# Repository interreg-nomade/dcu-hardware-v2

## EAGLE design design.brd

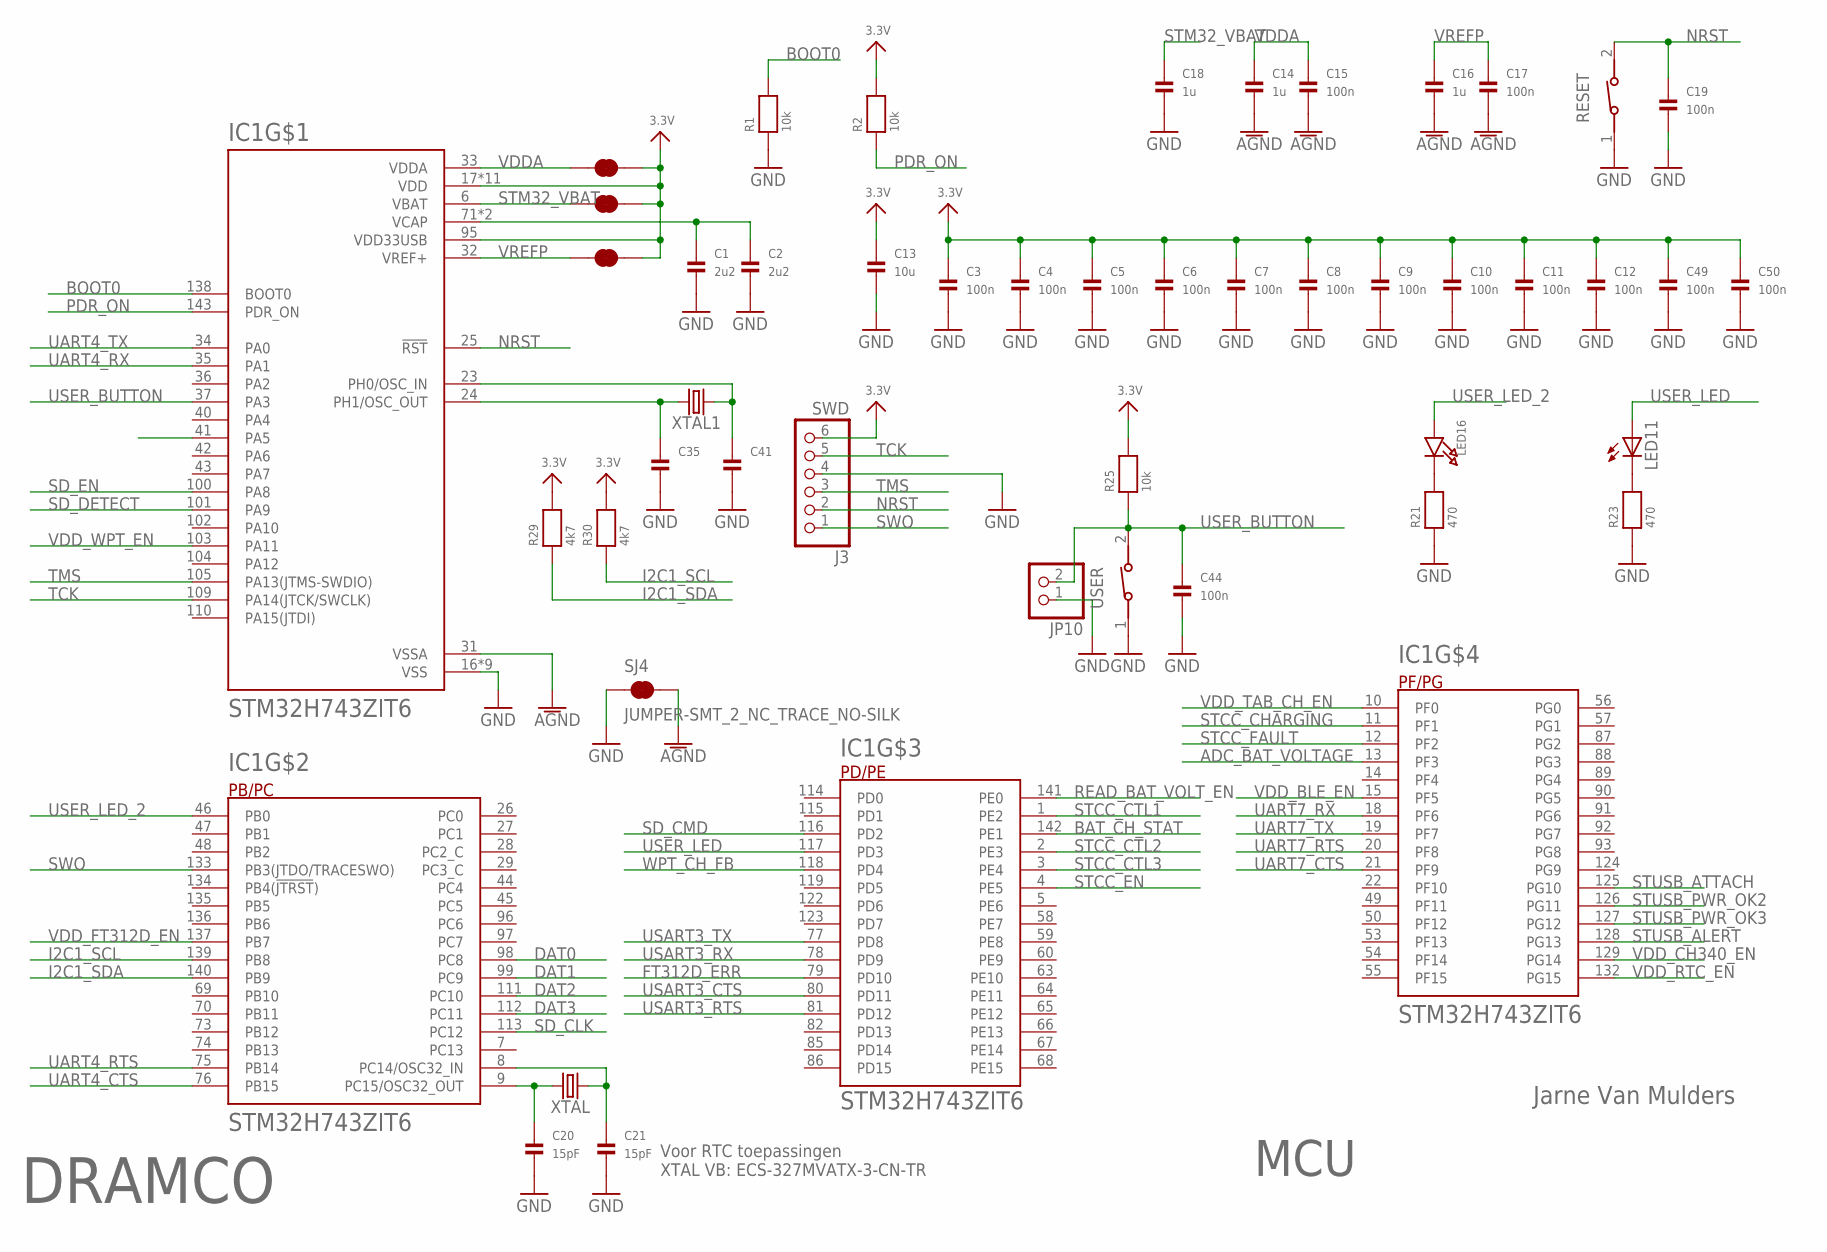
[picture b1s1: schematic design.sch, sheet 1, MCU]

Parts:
C1, C2: 2u2; 0805
C3, C4, C5, C6, C7, C8, C9, C10, C11, C12, C15, C17, C19, C44, C49, C50: 100n; 0603
C13: 10u; 0805
C14, C16, C18: 1u; 0603
C20, C21: 15pF; 0603
C35, C41: CAP_CERAMIC0603; 0603
IC1: STM32H743ZIT6; QFP50P2200X2200X160-144N
J3: SWD; 1X06_ROUND
JP10: HEADER-1X2ROUND; 1X02_ROUND
LED11: LED3MM
LED16: LED0805; CHIPLED_0805
R1, R2, R25: 10k; 0603
R21, R23: 470; 0603
R29, R30: 4k7; 0603
RESET: 434111043826
SJ1, SJ2, SJ3, SJ4: JUMPER-SMT_2_NC_TRACE_NO-SILK; SMT-JUMPER_2_NC_TRACE_NO-SILK
USER: 434111043826
XTAL, XTAL1: CRYSTALSMD-3.2X2.5; CRYSTAL-SMD-3.2X2.5MM

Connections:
3.3V: C3.1, C4.1, C5.1, C6.1, C7.1, C8.1, C9.1, C10.1, C11.1, C12.1, C13.1, C49.1, C50.1, IC1.17 (VDD), IC1.30 (VDD), IC1.39 (VDD), IC1.52 (VDD), IC1.62 (VDD), IC1.72 (VDD), IC1.84 (VDD), IC1.95 (VDD33USB), IC1.108 (VDD), IC1.121 (VDD), IC1.131 (VDD), IC1.144 (VDD), J3.6, R2.2, R25.2, R29.2, R30.2, SJ1.2, SJ2.2, SJ3.2; also elsewhere on the board
ADC_BAT_VOLTAGE: IC1.13 (PF3); also elsewhere on the board
AGND: C14.2, C15.2, C16.2, C17.2, IC1.31 (VSSA), SJ4.2
BAT_CH_STAT: IC1.142 (PE1); also elsewhere on the board
BOOT0: IC1.138 (BOOT0), R1.2
DAT0: IC1.98 (PC8); also elsewhere on the board
DAT1: IC1.99 (PC9); also elsewhere on the board
DAT2: IC1.111 (PC10); also elsewhere on the board
DAT3: IC1.112 (PC11); also elsewhere on the board
FT312D_ERR: IC1.79 (PD10); also elsewhere on the board
GND: C1.2, C2.2, C3.2, C4.2, C5.2, C6.2, C7.2, C8.2, C9.2, C10.2, C11.2, C12.2, C13.2, C18.2, C19.2, C20.2, C21.2, C35.2, C41.2, C44.2, C49.2, C50.2, IC1.16 (VSS), IC1.38 (VSS), IC1.51 (VSS), IC1.61 (VSS), IC1.83 (VSS), IC1.94 (VSS), IC1.107 (VSS), IC1.120 (VSS), IC1.130 (VSS), J3.4, JP10.1, R1.1, R21.1, R23.1, RESET.1, SJ4.1, USER.1; also elsewhere on the board
I2C1_SCL: IC1.139 (PB8), R30.1; also elsewhere on the board
I2C1_SDA: IC1.140 (PB9), R29.1; also elsewhere on the board
unnamed: C1.1, C2.1, IC1.71 (VCAP), IC1.106 (VCAP)
unnamed: C20.1, IC1.9 (PC15/OSC32_OUT), XTAL.3 (2)
unnamed: C21.1, IC1.8 (PC14/OSC32_IN), XTAL.1
unnamed: LED16.C, R21.2
unnamed: C35.1, IC1.24 (PH1/OSC_OUT), XTAL1.3 (2)
unnamed: LED11.K (C), R23.2
unnamed: C41.1, IC1.23 (PH0/OSC_IN), XTAL1.1
NRST: C19.1, IC1.25 (!RST), J3.2, RESET.2
PDR_ON: IC1.143 (PDR_ON), R2.1
READ_BAT_VOLT_EN: IC1.141 (PE0); also elsewhere on the board
SD_CLK: IC1.113 (PC12); also elsewhere on the board
SD_CMD: IC1.116 (PD2); also elsewhere on the board
SD_DETECT: IC1.101 (PA9); also elsewhere on the board
SD_EN: IC1.100 (PA8); also elsewhere on the board
STCC_CHARGING: IC1.11 (PF1); also elsewhere on the board
STCC_CTL1: IC1.1 (PE2); also elsewhere on the board
STCC_CTL2: IC1.2 (PE3); also elsewhere on the board
STCC_CTL3: IC1.3 (PE4); also elsewhere on the board
STCC_EN: IC1.4 (PE5); also elsewhere on the board
STCC_FAULT: IC1.12 (PF2); also elsewhere on the board
STM32_VBAT: C18.1, IC1.6 (VBAT), SJ2.1
STUSB_ALERT: IC1.128 (PG13); also elsewhere on the board
STUSB_ATTACH: IC1.125 (PG10); also elsewhere on the board
STUSB_PWR_OK2: IC1.126 (PG11); also elsewhere on the board
STUSB_PWR_OK3: IC1.127 (PG12); also elsewhere on the board
SWO: IC1.133 (PB3(JTDO/TRACESWO)), J3.1
TCK: IC1.109 (PA14(JTCK/SWCLK)), J3.5
TMS: IC1.105 (PA13(JTMS-SWDIO)), J3.3
UART4_CTS: IC1.76 (PB15); also elsewhere on the board
UART4_RTS: IC1.75 (PB14); also elsewhere on the board
UART4_RX: IC1.35 (PA1); also elsewhere on the board
UART4_TX: IC1.34 (PA0); also elsewhere on the board
UART7_CTS: IC1.21 (PF9); also elsewhere on the board
UART7_RTS: IC1.20 (PF8); also elsewhere on the board
UART7_RX: IC1.18 (PF6); also elsewhere on the board
UART7_TX: IC1.19 (PF7); also elsewhere on the board
USART3_CTS: IC1.80 (PD11); also elsewhere on the board
USART3_RTS: IC1.81 (PD12); also elsewhere on the board
USART3_RX: IC1.78 (PD9); also elsewhere on the board
USART3_TX: IC1.77 (PD8); also elsewhere on the board
USER_BUTTON: C44.1, IC1.37 (PA3), JP10.2, R25.1, USER.2
USER_LED: IC1.117 (PD3), LED11.A
USER_LED_2: IC1.46 (PB0), LED16.A
VDDA: C14.1, C15.1, IC1.33 (VDDA), SJ3.1
VDD_BLE_EN: IC1.15 (PF5); also elsewhere on the board
VDD_CH340_EN: IC1.129 (PG14); also elsewhere on the board
VDD_FT312D_EN: IC1.137 (PB7); also elsewhere on the board
VDD_NRF_EN: IC1.41 (PA5)
VDD_RTC_EN: IC1.132 (PG15); also elsewhere on the board
VDD_TAB_CH_EN: IC1.10 (PF0); also elsewhere on the board
VDD_WPT_EN: IC1.103 (PA11); also elsewhere on the board
VREFP: C16.1, C17.1, IC1.32 (VREF+), SJ1.1
WPT_CH_FB: IC1.118 (PD4); also elsewhere on the board

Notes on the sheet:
Voor RTC toepassingen XTAL VB: ECS-327MVATX-3-CN-TR
MCU
Jarne Van Mulders
DRAMCO

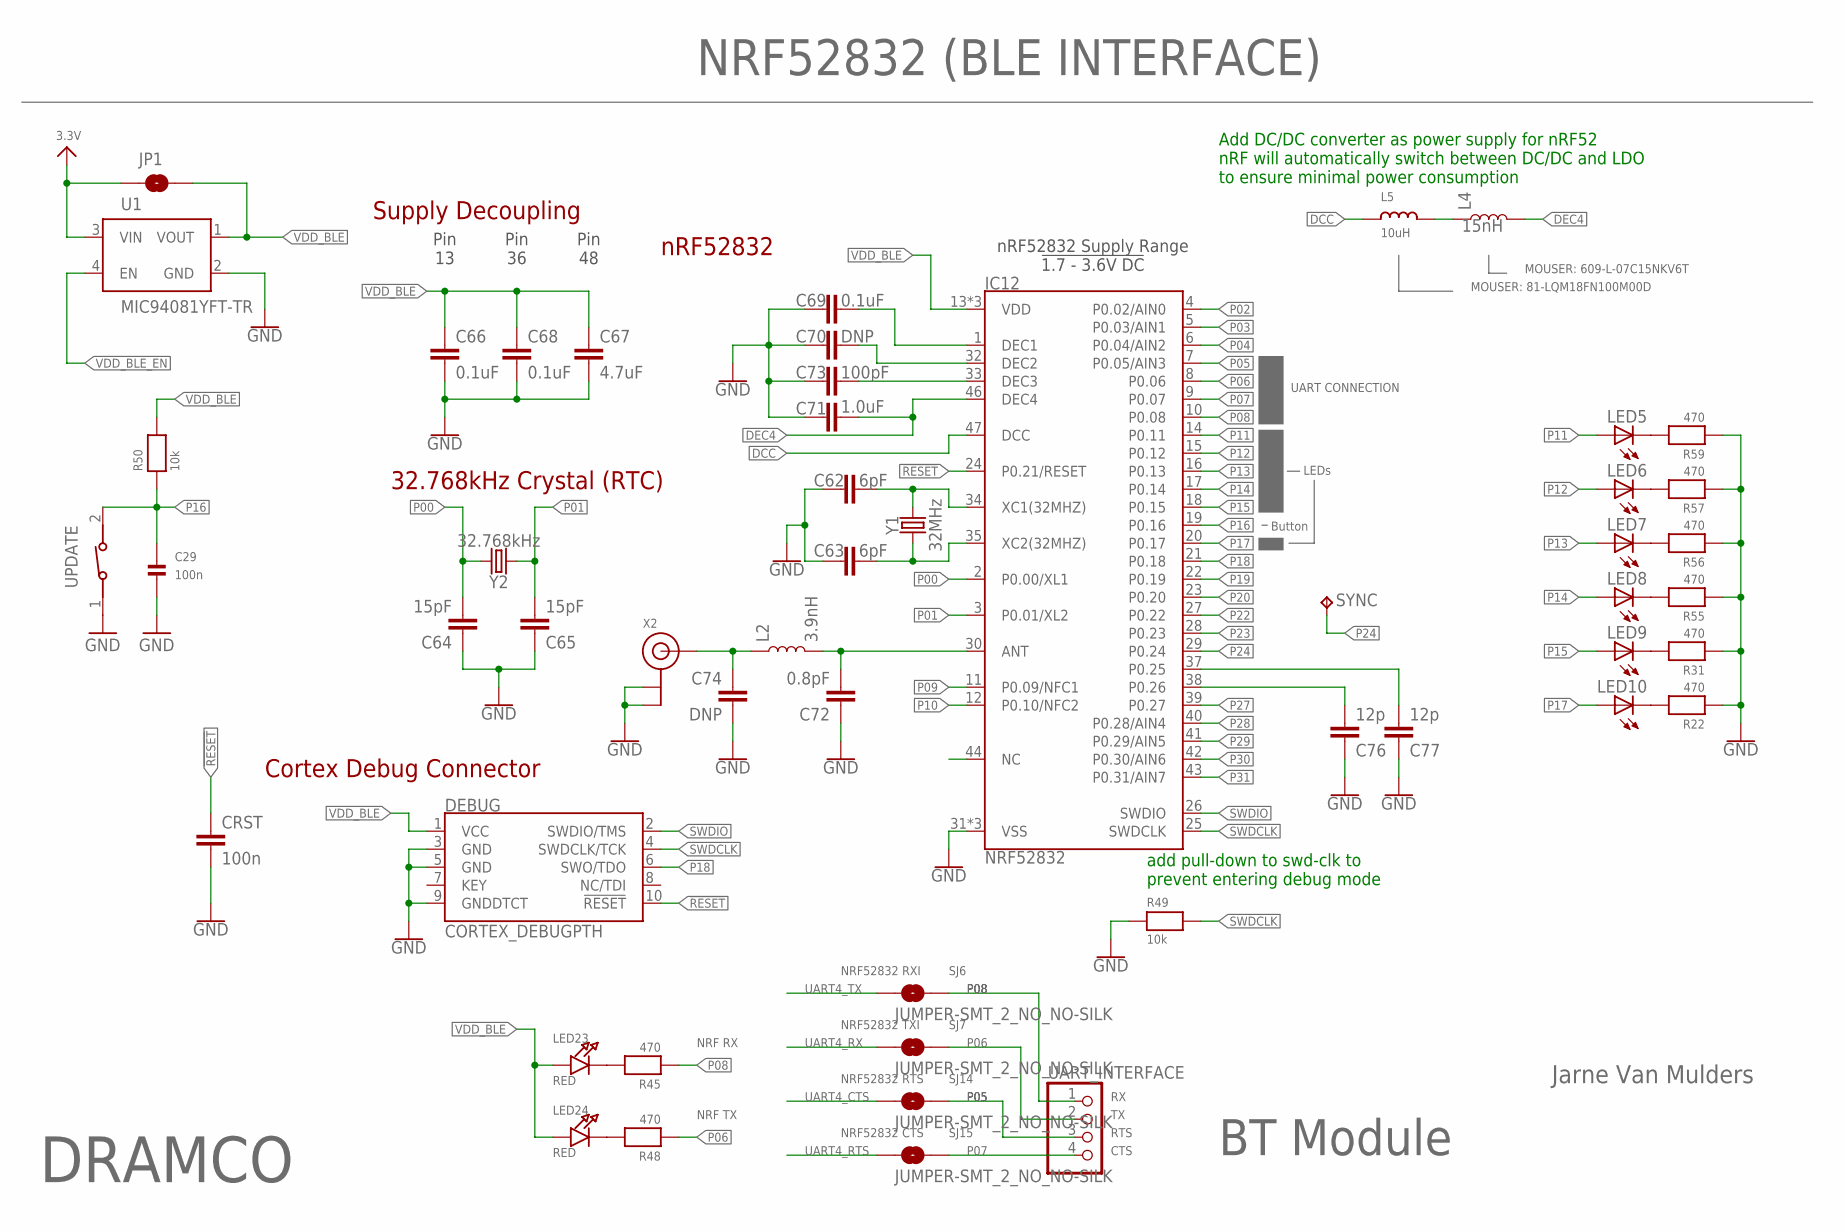
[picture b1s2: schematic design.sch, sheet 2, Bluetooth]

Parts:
C29: 100n; 0603
C62, C63: 6pF; 0402
C64, C65: 15pF; 0402
C66, C68, C69: 0.1uF; 0402
C67: 4.7uF; 0603
C70, C74: DNP; 0402
C71: 1.0uF; 0402
C72: 0.8pF; 0402
C73: 100pF; 0402
C76, C77: 12p; 0402
CRST: 100n; C0603
DEBUG: CORTEX_DEBUGPTH; 2X5-PTH-1.27MM
IC12: NRF52832; QFN48-6X6MM
JP1: JUMPER-SMT_2_NO_NO-SILK; SMT-JUMPER_2_NO_NO-SILK
L2: 3.9nH; 0402
L4: 15nH; 0402
L5: 10uH; _0603MP
LED5, LED6, LED7, LED8, LED9, LED10: LED3MM
LED23, LED24: RED; CHIPLED_0805
R22, R31, R45, R48, R55, R56, R57, R59: 470; 0603
R49, R50: 10k; 0603
SJ6, SJ7, SJ14, SJ15: JUMPER-SMT_2_NO_NO-SILK; SMT-JUMPER_2_NO_NO-SILK
SYNC: TPTP09R; TP09R
U1: MIC94081YFT-TR; IC_MIC94081YFT-TR
UART_INTERFACE: HEADER-1X4ROUND; 1X04_ROUND
UPDATE: 434111043826
X2: ANTENNA_U.FL; U.FL
Y1: 32MHz; CRYSTAL-SMD-2.0X1.6MM
Y2: 32.768kHz; CRYSTAL-SMD-3.2X1.5MM

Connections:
3.3V: JP1.1, U1.3 (VIN); also elsewhere on the board
!RESET!: CRST.1, DEBUG.10 (!RESET), IC12.24 (P0.21/RESET)
ANT: C72.2, IC12.30 (ANT), L2.2
DCC: IC12.47 (DCC), L5.1
DEC4: C71.2, IC12.46 (DEC4), L4.2
DEC5: C69.2, IC12.1 (DEC1)
DEC6: C70.2, IC12.32 (DEC2)
DEC8: C73.2, IC12.33 (DEC3)
GND: C29.2, C62.1, C63.2, C64.1, C65.1, C66.2, C67.2, C68.2, C69.1, C70.1, C71.1, C72.1, C73.1, C74.2, C76.1, C77.1, CRST.2, DEBUG.3 (GND), DEBUG.5 (GND), DEBUG.9 (GNDDTCT), IC12.31 (VSS), IC12.45 (VSS), IC12.EP (VSS), R22.1, R31.1, R49.1, R55.1, R56.1, R57.1, R59.1, U1.2 (GND), UPDATE.1, X2.1 (GND), X2.2 (GND); also elsewhere on the board
unnamed: LED10.K (C), R22.2
unnamed: LED9.K (C), R31.2
unnamed: LED8.K (C), R55.2
unnamed: C74.1, L2.1, X2.3 (SIGNAL)
unnamed: LED7.K (C), R56.2
unnamed: LED6.K (C), R57.2
unnamed: LED23.C, R45.2
unnamed: C77.2, IC12.37 (P0.25)
unnamed: LED24.C, R48.2
unnamed: L4.1, L5.2
unnamed: LED5.K (C), R59.2
NC: IC12.44 (NC)
P00: C64.2, IC12.2 (P0.00/XL1), Y2.P$2 (2)
P01: C65.2, IC12.3 (P0.01/XL2), Y2.P$1 (1)
P02: IC12.4 (P0.02/AIN0)
P03: IC12.5 (P0.03/AIN1)
P04: IC12.6 (P0.04/AIN2)
P05: IC12.7 (P0.05/AIN3), SJ14.2, UART_INTERFACE.3
P06: IC12.8 (P0.06), R48.1, SJ7.2, UART_INTERFACE.2
P07: IC12.9 (P0.07), SJ15.2, UART_INTERFACE.4
P08: IC12.10 (P0.08), R45.1, SJ6.2, UART_INTERFACE.1
P09: IC12.11 (P0.09/NFC1)
P10: IC12.12 (P0.10/NFC2)
P11: IC12.14 (P0.11), LED5.A
P12: IC12.15 (P0.12), LED6.A
P13: IC12.16 (P0.13), LED7.A
P14: IC12.17 (P0.14), LED8.A
P15: IC12.18 (P0.15), LED9.A
P16: C29.1, IC12.19 (P0.16), R50.1, UPDATE.2
P17: IC12.20 (P0.17), LED10.A
P18: DEBUG.6 (SWO/TDO), IC12.21 (P0.18)
P19: IC12.22 (P0.19)
P20: IC12.23 (P0.20)
P22: IC12.27 (P0.22)
P23: IC12.28 (P0.23)
P24: IC12.29 (P0.24), SYNC.TP
P26: C76.2, IC12.38 (P0.26)
P27: IC12.39 (P0.27)
P28: IC12.40 (P0.28/AIN4)
P29: IC12.41 (P0.29/AIN5)
P30: IC12.42 (P0.30/AIN6)
P31: IC12.43 (P0.31/AIN7)
SWDCLK: DEBUG.4 (SWDCLK/TCK), IC12.25 (SWDCLK), R49.2
SWDIO: DEBUG.2 (SWDIO/TMS), IC12.26 (SWDIO)
UART4_CTS: SJ14.1; also elsewhere on the board
UART4_RTS: SJ15.1; also elsewhere on the board
UART4_RX: SJ7.1; also elsewhere on the board
UART4_TX: SJ6.1; also elsewhere on the board
VDD_BLE: C66.1, C67.1, C68.1, DEBUG.1 (VCC), IC12.13 (VDD), IC12.36 (VDD), IC12.48 (VDD), JP1.2, LED23.A, LED24.A, R50.2, U1.1 (VOUT)
VDD_BLE_EN: U1.4 (EN); also elsewhere on the board
XC1: C62.2, IC12.34 (XC1(32MHZ)), Y1.3 (2)
XC2: C63.1, IC12.35 (XC2(32MHZ)), Y1.1

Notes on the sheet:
BT Module
Jarne Van Mulders
DRAMCO
NRF52832 (BLE INTERFACE)
Pin 13
Pin 36
Pin 48
nRF52832
32.768kHz Crystal (RTC)
Supply Decoupling
Cortex Debug Connector
nRF52832 Supply Range !1.7 - 3.6V DC!
Add DC/DC converter as power supply for nRF52 nRF will automatically switch between DC/DC and LDO to ensure minimal power consumption
add pull-down to swd-clk to prevent entering debug mode
NRF52832 RXI
NRF52832 TXI
NRF52832 RTS
NRF52832 CTS
MOUSER: 81-LQM18FN100M00D
MOUSER: 609-L-07C15NKV6T
NRF RX
NRF TX
RTS
CTS
UART CONNECTION
LEDs
Button

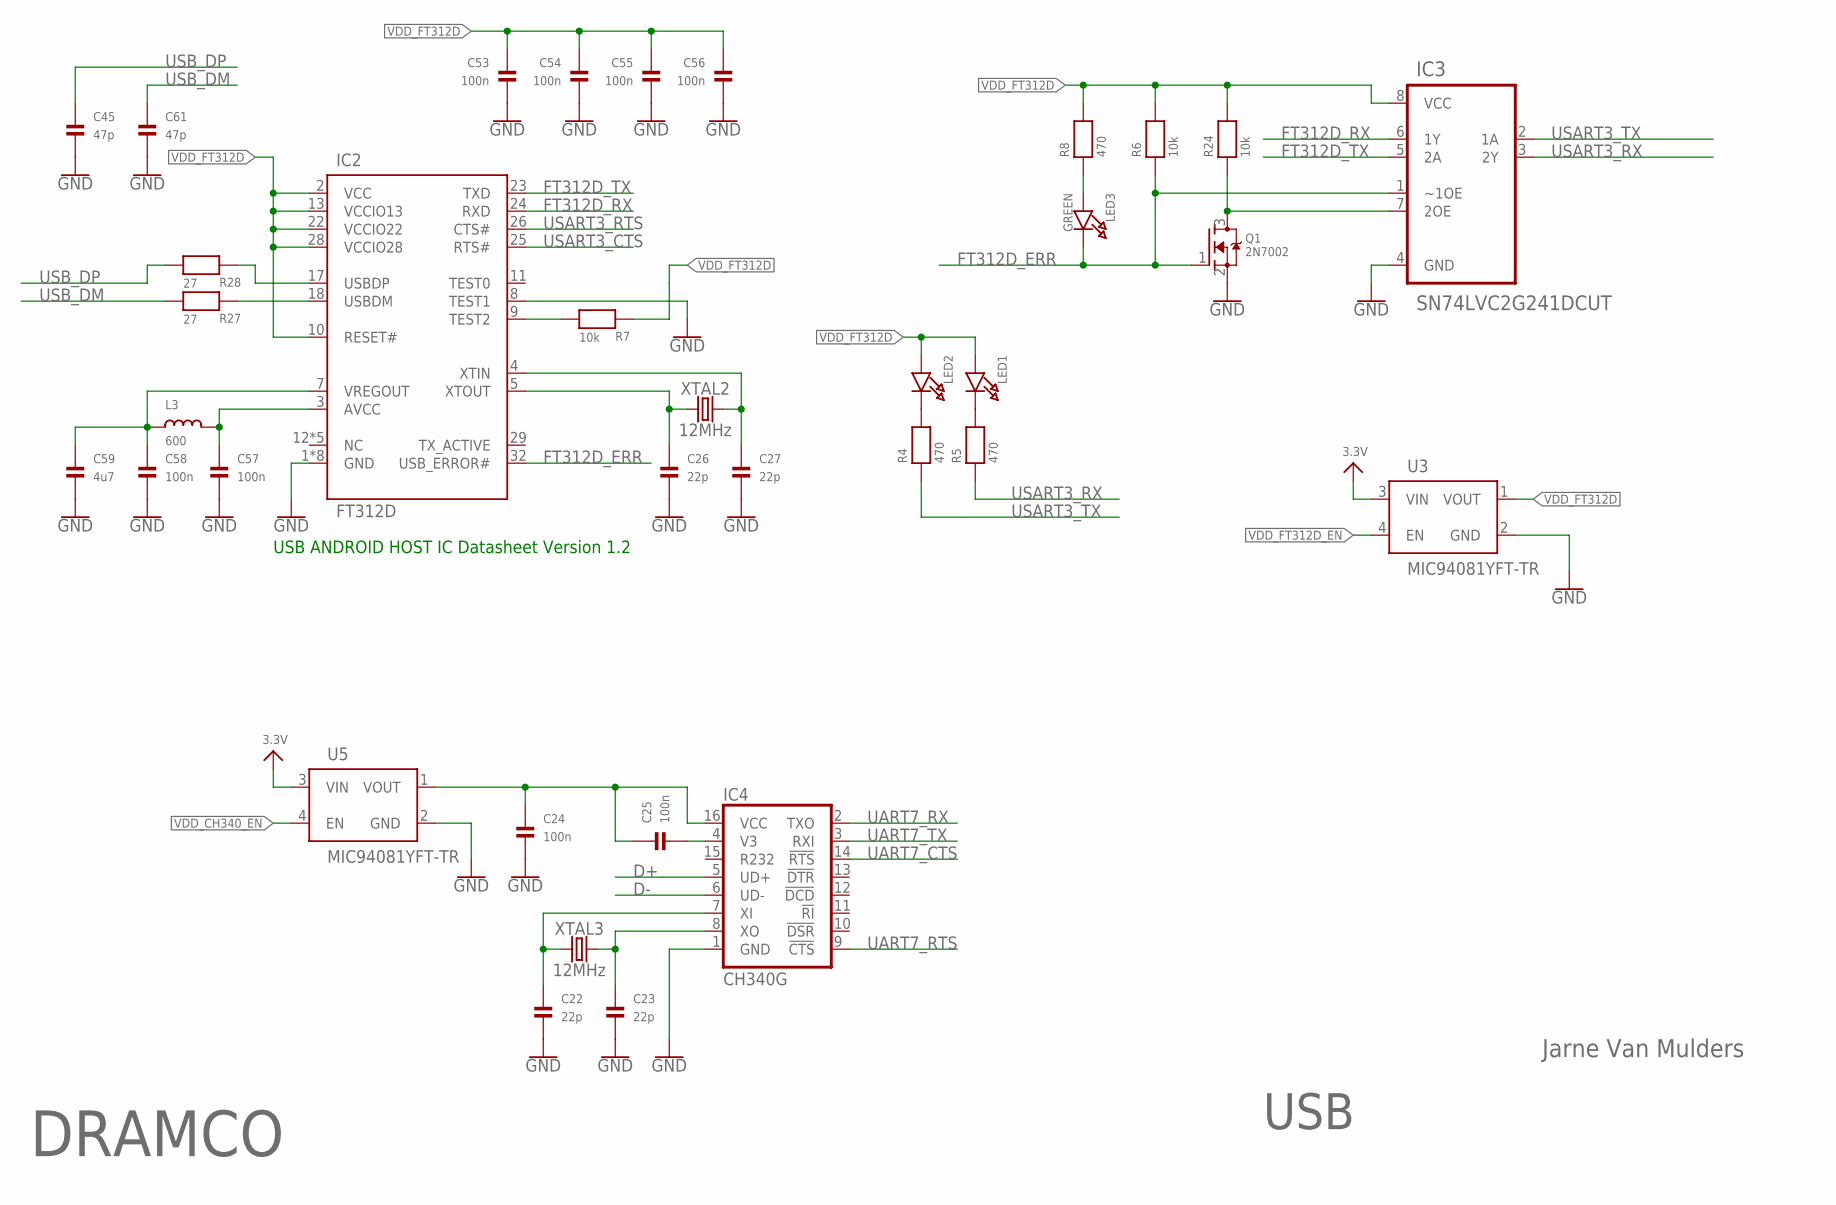
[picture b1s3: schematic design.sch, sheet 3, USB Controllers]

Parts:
C22, C23, C26, C27: 22p; 0603
C24, C25, C53, C54, C55, C56, C57, C58: 100n; 0603
C45, C61: 47p; 0603
C59: 4u7; 0603
IC2: FT312D; QFP80P900X900X160-32N
IC3: SN74LVC2G241DCUT; SOP50P310X90-8N
IC4: CH340G; SO016
L3: 600; 0603
LED1, LED2: LED0805; CHIPLED_0805
LED3: GREEN; CHIPLED_0805
Q1: 2N7002; SOT23-WIDE
R4, R5, R8: 470; 0603
R6, R7, R24: 10k; 0603
R27, R28: 27; 0603
U3, U5: MIC94081YFT-TR; IC_MIC94081YFT-TR
XTAL2, XTAL3: 12MHz; CRYSTAL-SMD-3.2X2.5MM

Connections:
3.3V: U3.3 (VIN), U5.3 (VIN); also elsewhere on the board
D+: IC4.5 (UD+); also elsewhere on the board
D-: IC4.6 (UD-); also elsewhere on the board
FT312D_ERR: IC2.32 (USB_ERROR#), IC3.1 (~1OE), LED3.C, Q1.1 (G), R6.1; also elsewhere on the board
FT312D_RX: IC2.24 (RXD), IC3.6 (1Y)
FT312D_TX: IC2.23 (TXD), IC3.5 (2A)
GND: C22.2, C23.2, C24.2, C26.2, C27.2, C45.2, C53.2, C54.2, C55.2, C56.2, C57.2, C58.2, C59.2, C61.2, IC2.1 (GND), IC2.6 (GND), IC2.8 (TEST1), IC2.14 (GND), IC2.15 (GND), IC2.16 (GND), IC2.19 (GND), IC2.27 (GND), IC2.33 (GND), IC3.4 (GND), IC4.1 (GND), Q1.2 (S), U3.2 (GND), U5.2 (GND); also elsewhere on the board
unnamed: LED2.C, R4.2
unnamed: LED1.C, R5.2
unnamed: C27.1, IC2.4 (XTIN), XTAL2.3 (2)
unnamed: C26.1, IC2.5 (XTOUT), XTAL2.1
unnamed: C24.1, C25.1, IC4.16 (VCC), U5.1 (VOUT)
unnamed: LED3.A, R8.1
unnamed: IC2.9 (TEST2), R7.1
unnamed: IC3.7 (2OE), Q1.3 (D), R24.1
unnamed: C22.1, IC4.7 (XI), XTAL3.1
unnamed: C23.1, IC4.8 (XO), XTAL3.3 (2)
unnamed: C25.2, IC4.4 (V3)
unnamed: C58.1, C59.1, IC2.7 (VREGOUT), L3.1
unnamed: C57.1, IC2.3 (AVCC), L3.2
unnamed: IC2.18 (USBDM), R27.2
unnamed: IC2.17 (USBDP), R28.2
UART7_CTS: IC4.14 (!RTS); also elsewhere on the board
UART7_RTS: IC4.9 (!CTS); also elsewhere on the board
UART7_RX: IC4.2 (TXO); also elsewhere on the board
UART7_TX: IC4.3 (RXI); also elsewhere on the board
USART3_CTS: IC2.25 (RTS#); also elsewhere on the board
USART3_RTS: IC2.26 (CTS#); also elsewhere on the board
USART3_RX: IC3.3 (2Y), R5.1; also elsewhere on the board
USART3_TX: IC3.2 (1A), R4.1; also elsewhere on the board
USB_DM: C61.1, R27.1; also elsewhere on the board
USB_DP: C45.1, R28.1; also elsewhere on the board
VDD_CH340_EN: U5.4 (EN); also elsewhere on the board
VDD_FT312D: C53.1, C54.1, C55.1, C56.1, IC2.2 (VCC), IC2.10 (RESET#), IC2.13 (VCCIO13), IC2.22 (VCCIO22), IC2.28 (VCCIO28), IC3.8 (VCC), LED1.A, LED2.A, R6.2, R7.2, R8.2, R24.2, U3.1 (VOUT)
VDD_FT312D_EN: U3.4 (EN); also elsewhere on the board

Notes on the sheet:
USB ANDROID HOST IC Datasheet Version 1.2
USB
Jarne Van Mulders
DRAMCO

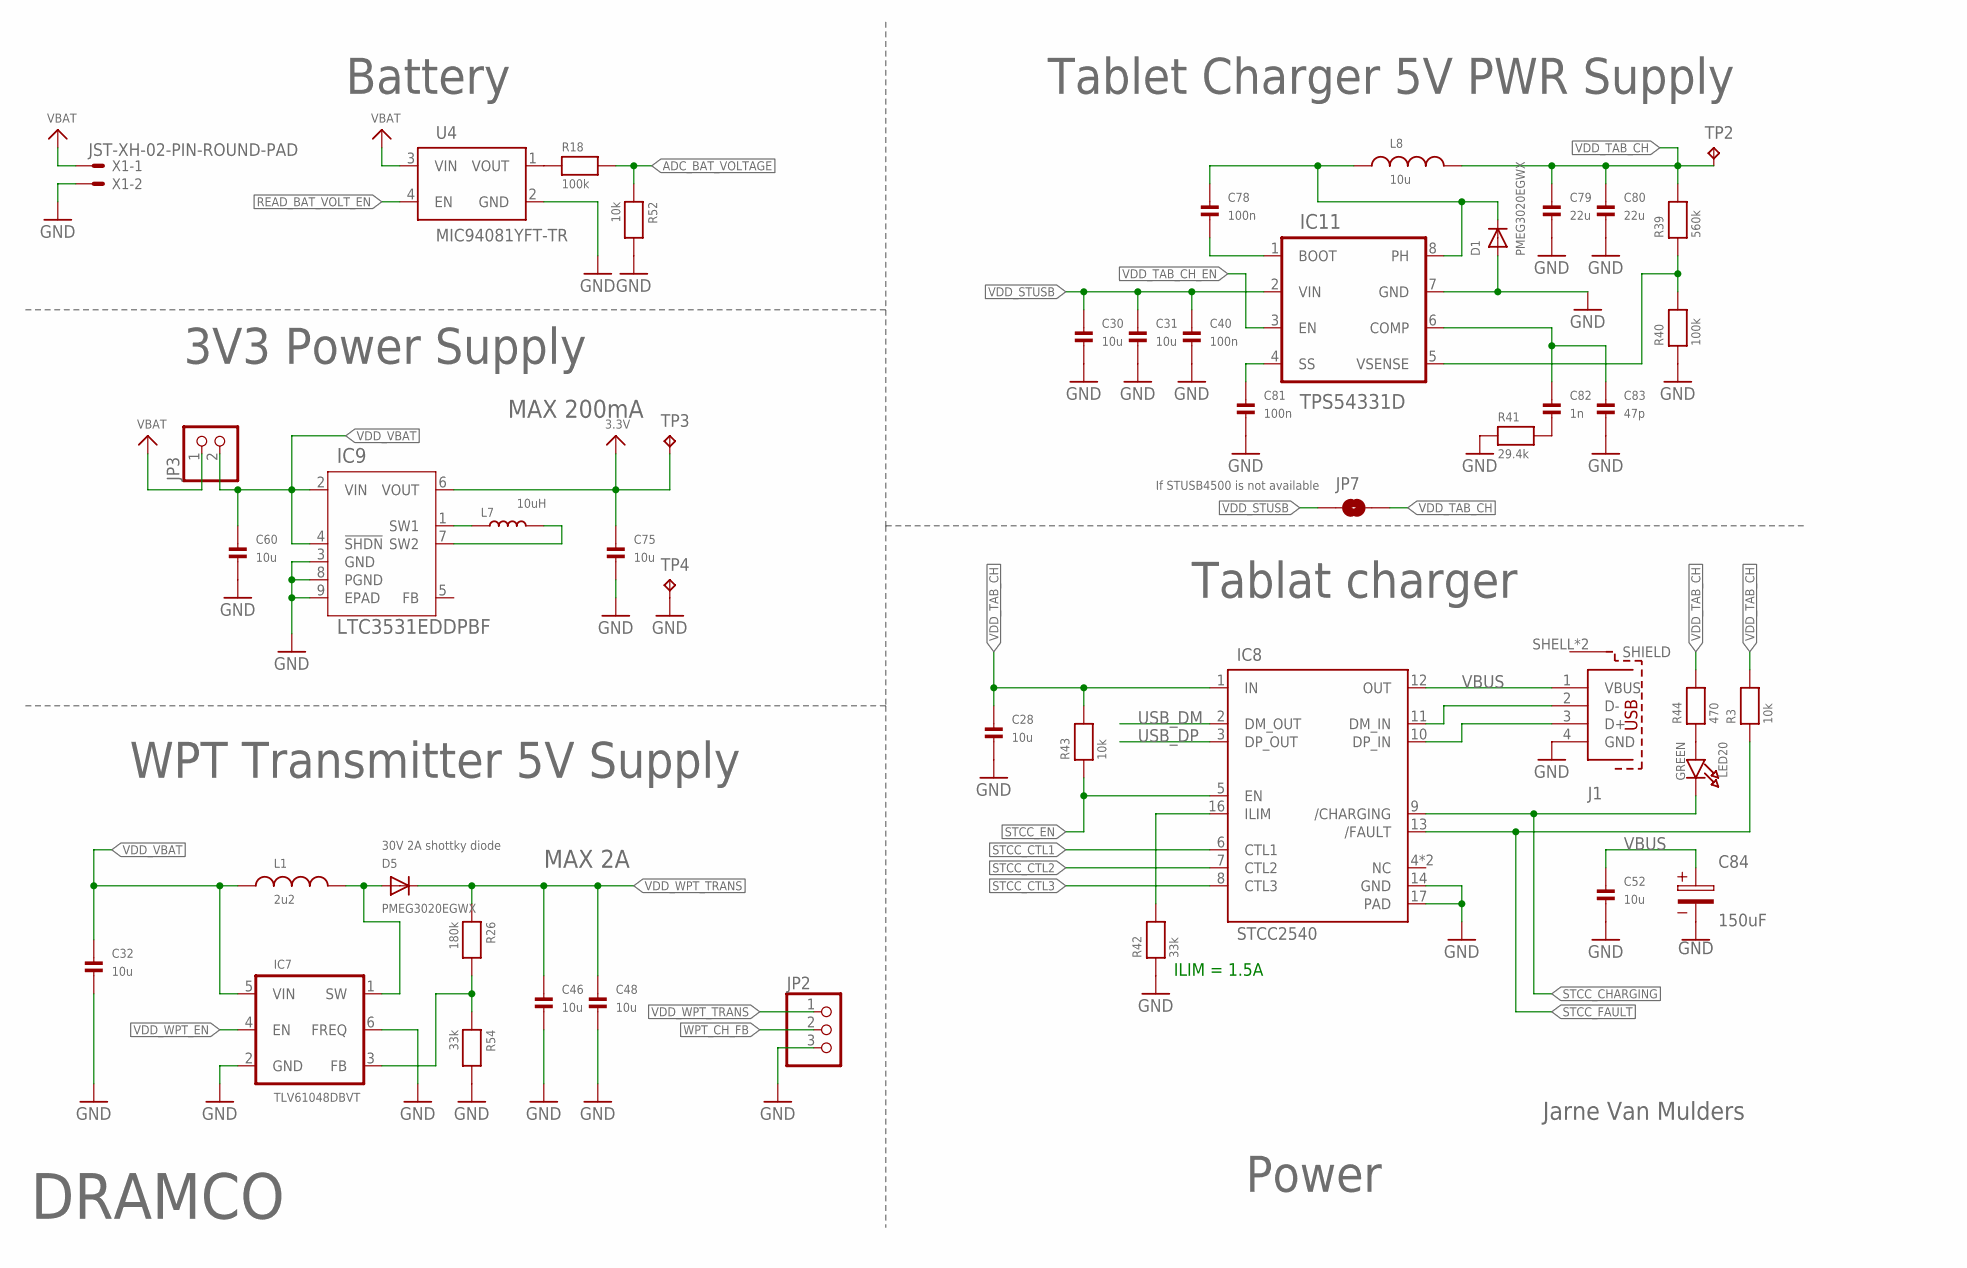
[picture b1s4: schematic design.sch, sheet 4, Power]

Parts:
C28, C30, C31, C32, C46, C48, C52, C60, C75: 10u; 0805
C40, C81: 100n; 0603
C78: 100n; 0402
C79, C80: 22u; 0805
C82: 1n; 0603
C83: 47p; 0603
C84: 150uF; 3.5X1.6X2.1(BXCXA)
D1, D5: PMEG3020EGWX; SOD-123
IC7: TLV61048DBVT; SOT95P280X145-6N
IC8: STCC2540; QFN50P300X300X80-17N
IC9: LTC3531EDDPBF; DFN-8_DD
IC11: TPS54331D; SOIC127P599X175-8N
J1: 614004190021
JP2: HEADER-1X3ROUND; 1X03_ROUND
JP3: HEADER-1X2ROUND; 1X02_ROUND
JP7: JUMPER-SMT_2_NO_NO-SILK; SMT-JUMPER_2_NO_NO-SILK
L1: 2u2; WE-MAIA_3020
L7: 10uH; MSS4020
L8: 10u; WE-MAIA_4030
LED20: GREEN; CHIPLED_0805
R3, R43, R52: 10k; 0603
R18, R40: 100k; 0603
R26: 180k; 0603
R39: 560k; 0603
R41: 29.4k; 0603
R42, R54: 33k; 0603
R44: 470; 0603
TP2, TP3, TP4: TPTP10R; TP10R
U4: MIC94081YFT-TR; IC_MIC94081YFT-TR
X1: JST-XH-02-PIN-ROUND-PAD; JST-XH-02-PACKAGE-ROUND-PAD

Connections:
3.3V: C75.1, IC9.6 (VOUT), TP3.TP; also elsewhere on the board
ADC_BAT_VOLTAGE: R18.2, R52.1; also elsewhere on the board
GND: C28.2, C30.2, C31.2, C32.2, C40.2, C46.2, C48.2, C52.2, C60.2, C75.2, C79.2, C80.2, C81.2, C83.2, C84.2, D1.A, IC7.2 (GND), IC7.6 (FREQ), IC8.14 (GND), IC8.17 (PAD), IC9.3 (GND), IC9.8 (PGND), IC9.9 (EPAD), IC11.7 (GND), J1.4 (GND), JP2.3, R40.1, R41.1, R42.1, R52.2, R54.2, TP4.TP, U4.2 (GND), X1.2; also elsewhere on the board
unnamed: LED20.A, R44.1
unnamed: C78.1, D1.C, IC11.8 (PH), L8.1
unnamed: D5.A, IC7.1 (SW), L1.2
unnamed: IC8.16 (ILIM), R42.2
unnamed: R18.1, U4.1 (VOUT)
unnamed: C81.1, IC11.4 (SS)
unnamed: IC7.3 (FB), R26.2, R54.1
unnamed: C78.2, IC11.1 (BOOT)
unnamed: IC8.11 (DM_IN), J1.2 (D-)
unnamed: IC8.10 (DP_IN), J1.3 (D+)
unnamed: C82.1, C83.1, IC11.6 (COMP)
unnamed: IC11.5 (VSENSE), R39.1, R40.2
unnamed: C82.2, R41.2
READ_BAT_VOLT_EN: U4.4 (EN); also elsewhere on the board
STCC_CHARGING: IC8.9 (/CHARGING), LED20.C; also elsewhere on the board
STCC_CTL1: IC8.6 (CTL1); also elsewhere on the board
STCC_CTL2: IC8.7 (CTL2); also elsewhere on the board
STCC_CTL3: IC8.8 (CTL3); also elsewhere on the board
STCC_EN: IC8.5 (EN), R43.1; also elsewhere on the board
STCC_FAULT: IC8.13 (/FAULT), R3.1; also elsewhere on the board
SW1: IC9.1 (SW1), L7.1
SW2: IC9.7 (SW2), L7.2
USB_DM: IC8.2 (DM_OUT); also elsewhere on the board
USB_DP: IC8.3 (DP_OUT); also elsewhere on the board
VBAT: JP3.1, U4.3 (VIN), X1.1; also elsewhere on the board
VBUS: C52.1, C84.1, IC8.12 (OUT), J1.1 (VBUS)
VDD_STUSB: C30.1, C31.1, C40.1, IC11.2 (VIN), JP7.1; also elsewhere on the board
VDD_TAB_CH: C28.1, C79.1, C80.1, IC8.1 (IN), JP7.2, L8.2, R3.2, R39.2, R43.2, R44.2, TP2.TP
VDD_TAB_CH_EN: IC11.3 (EN); also elsewhere on the board
VDD_VBAT: C32.1, C60.1, IC7.5 (VIN), IC9.2 (VIN), IC9.4 (!SHDN), JP3.2, L1.1
VDD_WPT_EN: IC7.4 (EN); also elsewhere on the board
VDD_WPT_TRANS: C46.1, C48.1, D5.C, JP2.1, R26.1
WPT_CH_FB: JP2.2; also elsewhere on the board

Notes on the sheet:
Power
Jarne Van Mulders
DRAMCO
MAX 200mA
30V 2A shottky diode
MAX 2A
3V3 Power Supply
Tablat charger
Battery
WPT Transmitter 5V Supply
Tablet Charger 5V PWR Supply
ILIM = 1.5A
If STUSB4500 is not available

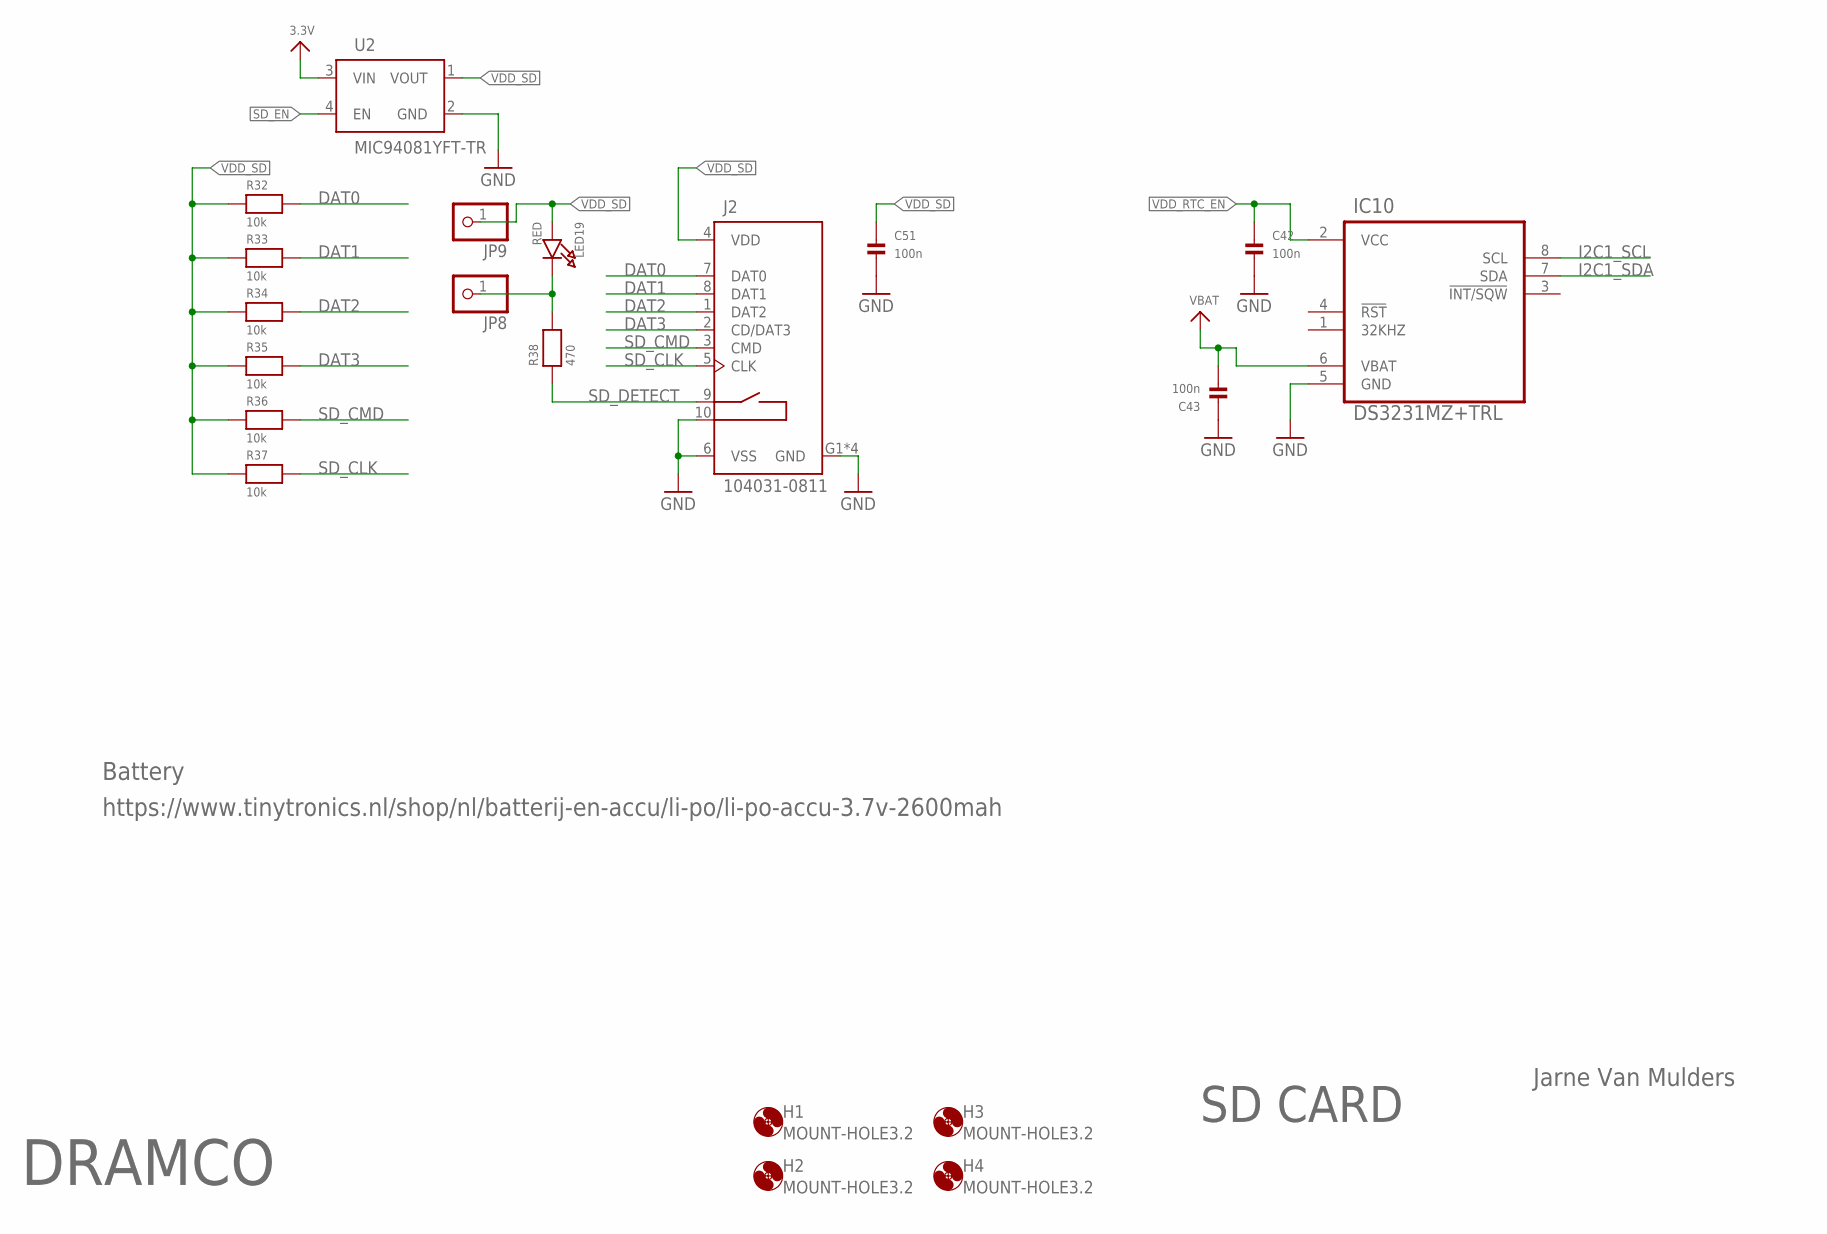
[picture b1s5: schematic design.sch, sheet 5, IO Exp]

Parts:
C42, C43, C51: 100n; 0603
H1, H2, H3, H4: MOUNT-HOLE3.2; 3,2
IC10: DS3231MZ+TRL; SOIC127P600X175-8N
J2: 104031-0811; MOLEX_104031-0811
JP8, JP9: HEADER-1X1ROUND; 1X01_ROUND
LED19: RED; CHIPLED_0805
R32, R33, R34, R35, R36, R37: 10k; 0603
R38: 470; 0603
U2: MIC94081YFT-TR; IC_MIC94081YFT-TR

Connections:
3.3V: U2.3 (VIN); also elsewhere on the board
DAT0: J2.7 (DAT0), R32.2; also elsewhere on the board
DAT1: J2.8 (DAT1), R33.2; also elsewhere on the board
DAT2: J2.1 (DAT2), R34.2; also elsewhere on the board
DAT3: J2.2 (CD/DAT3), R35.2; also elsewhere on the board
GND: C42.2, C43.1, C51.2, IC10.5 (GND), J2.6 (VSS), J2.10 (CARD_DET2), J2.G1 (GND), J2.G2 (GND), J2.G3 (GND), J2.G4 (GND), U2.2 (GND); also elsewhere on the board
I2C1_SCL: IC10.8 (SCL); also elsewhere on the board
I2C1_SDA: IC10.7 (SDA); also elsewhere on the board
unnamed: JP8.1, LED19.C, R38.2
SD_CLK: J2.5 (CLK), R37.2; also elsewhere on the board
SD_CMD: J2.3 (CMD), R36.2; also elsewhere on the board
SD_DETECT: J2.9 (CARD_DET1), R38.1; also elsewhere on the board
SD_EN: U2.4 (EN); also elsewhere on the board
VBAT: C43.2, IC10.6 (VBAT); also elsewhere on the board
VDD_RTC_EN: C42.1, IC10.2 (VCC); also elsewhere on the board
VDD_SD: C51.1, J2.4 (VDD), JP9.1, LED19.A, R32.1, R33.1, R34.1, R35.1, R36.1, R37.1, U2.1 (VOUT)

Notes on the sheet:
Jarne Van Mulders
DRAMCO
SD CARD
Battery
https://www.tinytronics.nl/shop/nl/batterij-en-accu/li-po/li-po-accu-3.7v-2600mah

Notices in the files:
parts and their libraries:
microbuilder: This work is placed in the public domain, and may be freely used for commercial and non-commercial work with the following conditions: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
SparkFun-IC-Comms: Licensing: Creative Commons ShareAlike 4.0 International - https://creativecommons.org/licenses/by-sa/4.0
